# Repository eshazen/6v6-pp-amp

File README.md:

# 10 WPC 6V6 push-pull amp

This is a proposed build of an amp for TV sound.  I've been using a
6V6 single-ended amp, which is OK but perhaps a little wimpy for this
application.  The Dynaco A-410 EL84/6V6 schematic looks like a nice,
classic option.

As of 2026-04-02:

DigiKey parts are about $560 including iron.

Tubes:

    JJ 6SL7 2 @ $26.95  $45
    JJ 6V6  4 @ $23.95  $96
    JJ GZ34 1 @ $21.95  $22
                 Total $163

PCBs from JLC almost $200 with shipping.
<br>PCBGOGO $178 with shipping
				 
So around $950 total without chassis. Amps are now expensive!

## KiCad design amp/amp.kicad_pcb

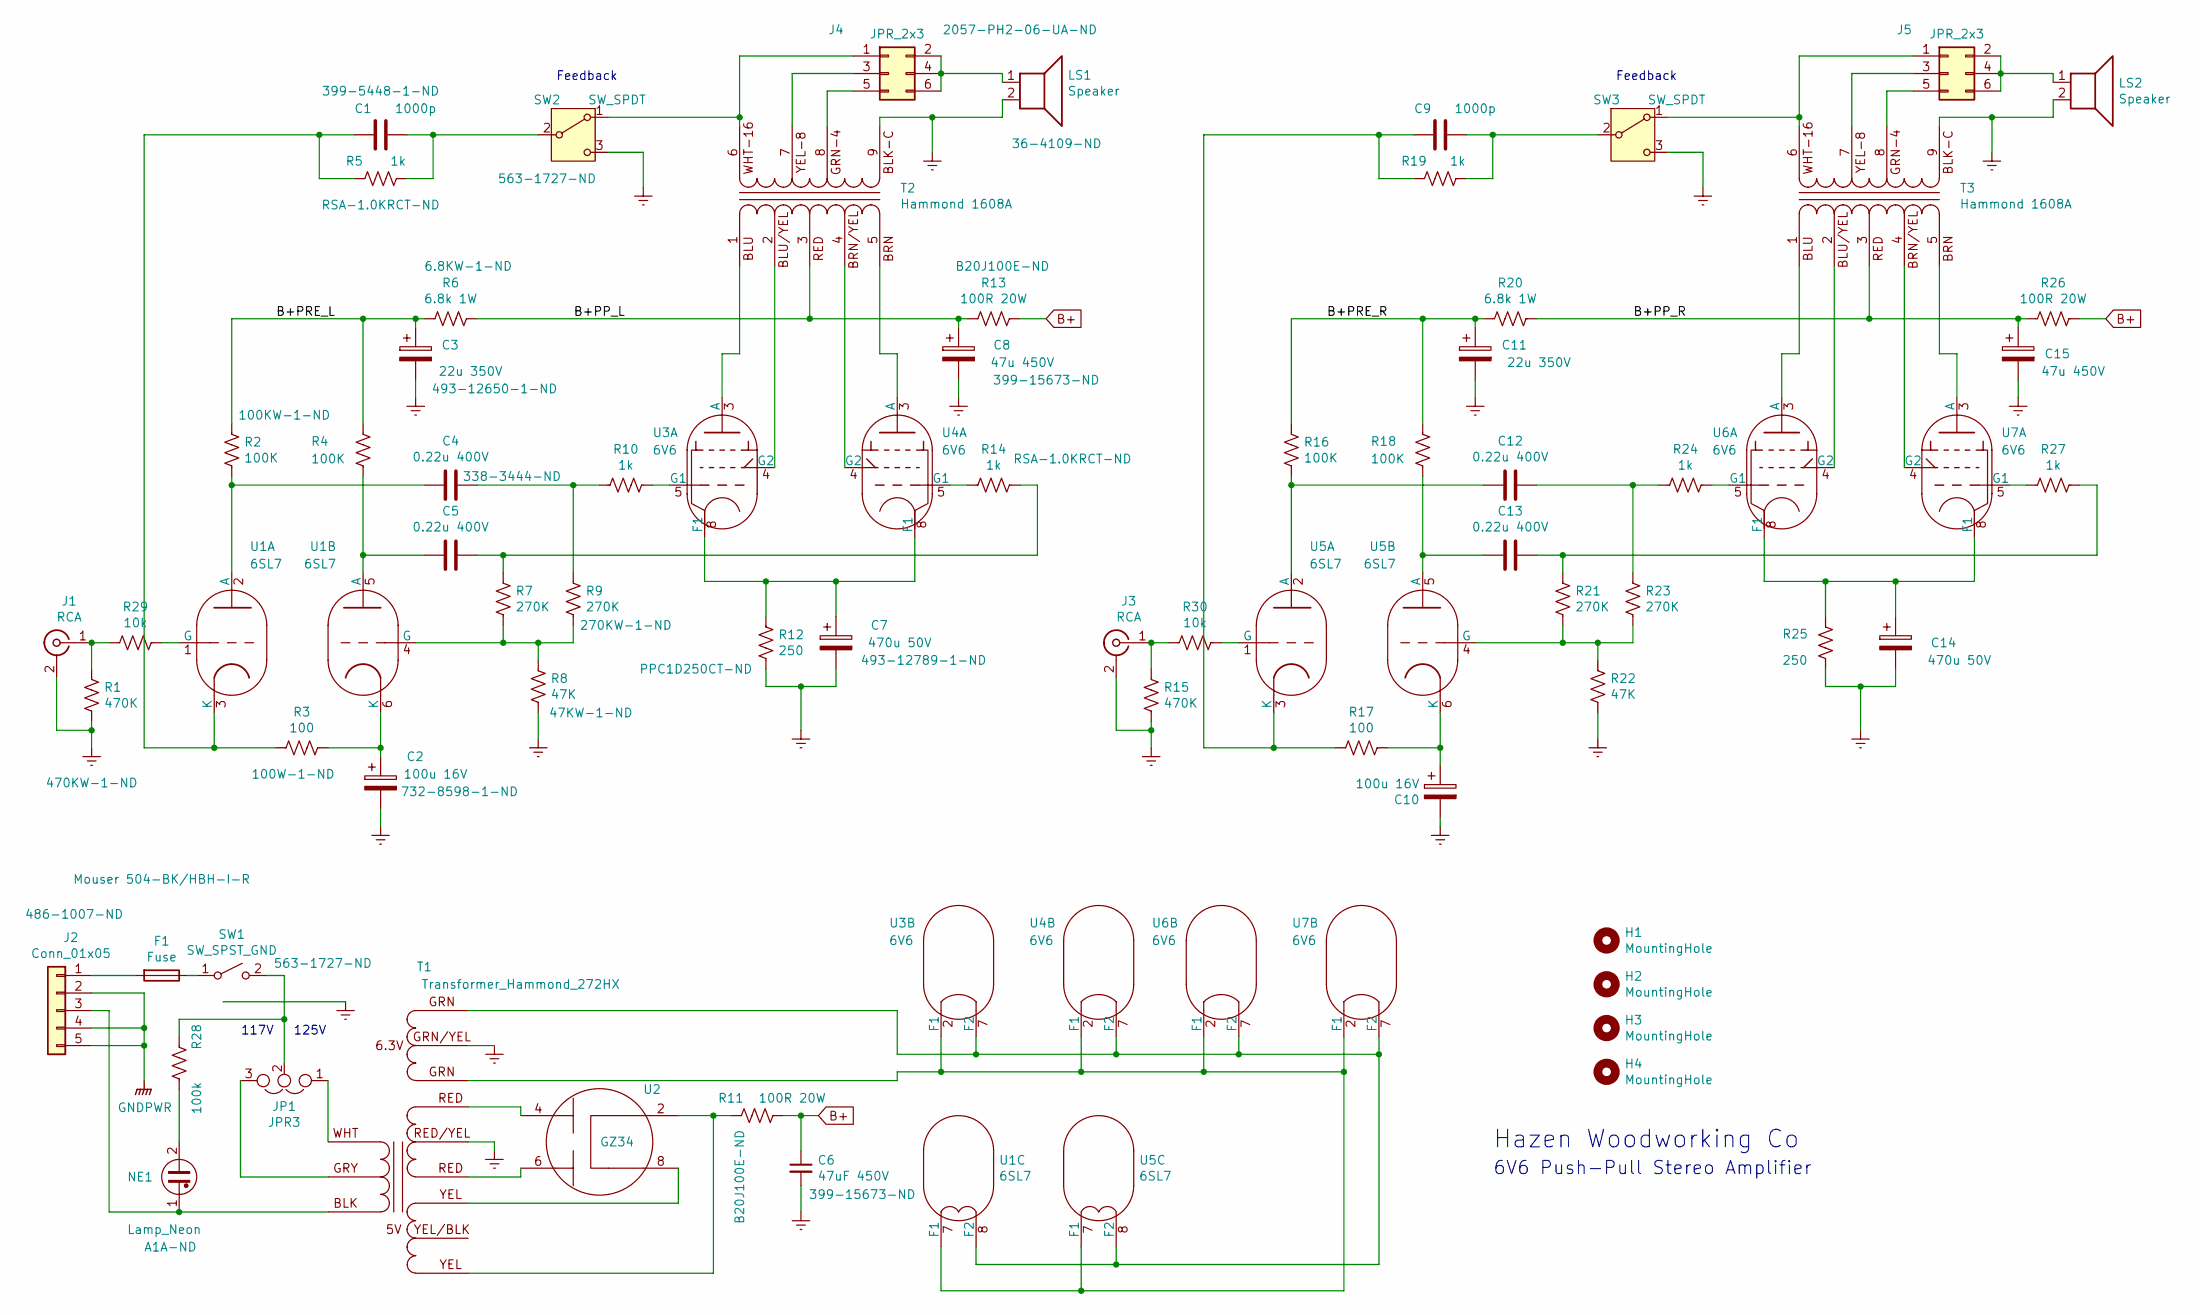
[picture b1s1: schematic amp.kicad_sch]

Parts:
C1, C9: 1000p; C_Rect_L7.2mm_W2.5mm_P5.00mm_FKS2_FKP2_MKS2_MKP2
C2, C10: 100u 16V; CP_Radial_D5.0mm_P2.00mm
C3, C11: 22u 350V; CP_Radial_D12.5mm_P5.00mm
C4, C5, C12, C13: 0.22u 400V; cap_rect_32x14_P18.3mm
C6: 47uF 450V; CP_Radial_D16.0mm_P7.50mm
C7, C14: 470u 50V; CP_Radial_D12.5mm_P5.00mm
C8, C15: 47u 450V; CP_Radial_D16.0mm_P7.50mm
F1: Fuse; HBH-I-R
H1, H2, H3, H4: MountingHole; Mtg6-32
J1, J3: RCA; PRJAN1X1
J2: Conn_01x05; GSP1.8101.1
J4, J5: JPR_2x3; PinHeader_2x03_P2.54mm_Vertical
JP1: JPR3; Molex_KK-396_A-41791-0003_1x03_P3.96mm_Vertical
LS1, LS2: Speaker; Keystone_4109
NE1: Lamp_Neon; A1A
R1, R15: 470K; R_Axial_DIN0411_L9.9mm_D3.6mm_P12.70mm_Horizontal
R2, R4, R16, R18: 100K; R_Axial_DIN0414_L11.9mm_D4.5mm_P15.24mm_Horizontal
R3, R17: 100; R_Axial_DIN0414_L11.9mm_D4.5mm_P15.24mm_Horizontal
R5, R10, R14, R19, R24, R27: 1k; R_Axial_DIN0411_L9.9mm_D3.6mm_P12.70mm_Horizontal
R6, R20: 6.8k 1W; R_Axial_DIN0414_L11.9mm_D4.5mm_P15.24mm_Horizontal
R7, R9, R21, R23: 270K; R_Axial_DIN0414_L11.9mm_D4.5mm_P15.24mm_Horizontal
R8, R22: 47K; R_Axial_DIN0411_L9.9mm_D3.6mm_P12.70mm_Horizontal
R11, R13, R26: 100R 20W; R_100R_20W_11x51mm
R12, R25: 250; R_Axial_DIN0414_L11.9mm_D4.5mm_P15.24mm_Horizontal
R28: 100k; R_Axial_DIN0414_L11.9mm_D4.5mm_P15.24mm_Horizontal
R29, R30: 10k; R_Axial_DIN0414_L11.9mm_D4.5mm_P15.24mm_Horizontal
SW1: SW_SPST_GND; 8GA1016-Z
SW2, SW3: SW_SPDT; 8GA1016-Z
T1: Transformer_Hammond_272HX; Hammond_272HX
T2, T3: Hammond 1608A; Hammond_1608A
U1, U5: 6SL7; Octal_Socket_P-ST8-193
U2: GZ34; Octal_Socket_P-ST8-193
U3, U4, U6, U7: 6V6; Octal_Socket_P-ST8-193

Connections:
/B+PP_L: C8.1, R6.1, R13.2, T2.3 (RED)
/B+PP_R: C15.1, R20.1, R26.2, T3.3 (RED)
/B+PRE_L: C3.1, R2.1, R4.1, R6.2
/B+PRE_R: C11.1, R16.1, R18.1, R20.2
B+: C6.1, R11.1, R13.1, R26.1
Earth: C2.2, C3.2, C6.2, C7.2, C8.2, C10.2, C11.2, C14.2, C15.2, J1.2 (Ext), J3.2 (Ext), LS1.2, LS2.2, R1.2, R8.2, R12.2, R15.2, R22.2, R25.2, SW1.4 (G1), SW2.3 (C), SW3.3 (C), T1.8 (SC), T1.11 (FC), T2.9 (BLK), T3.9 (BLK)
GNDPWR: J2.2, J2.4, J2.5
unnamed: C4.1, R9.1, R10.2
unnamed: C5.1, R7.1, R14.1
unnamed: C12.1, R23.1, R24.2
unnamed: C13.1, R21.1, R27.1
unnamed: J1.1 (In), R1.1, R29.2
unnamed: F1.2, J2.1
unnamed: J2.3, NE1.1, T1.3 (AB)
unnamed: J3.1 (In), R15.1, R30.2
unnamed: J4.1, SW2.1 (A), T2.6 (WHT)
unnamed: J4.2, J4.4, J4.6, LS1.1
unnamed: J4.3, T2.7 (YEL)
unnamed: J4.5, T2.8 (GRN)
unnamed: J5.1, SW3.1 (A), T3.6 (WHT)
unnamed: J5.2, J5.4, J5.6, LS2.1
unnamed: J5.3, T3.7 (YEL)
unnamed: J5.5, T3.8 (GRN)
unnamed: NE1.2, R28.1
unnamed: F1.1, SW1.1 (A)
unnamed: JP1.2, R28.2, SW1.2 (B)
unnamed: C1.1, R5.1, SW2.2 (B)
unnamed: C9.1, R19.1, SW3.2 (B)
unnamed: JP1.1, T1.1 (AA)
unnamed: JP1.3, T1.2 (AC)
unnamed: T1.10 (FA), U1.7 (F1), U3.2 (F1), U4.2 (F1), U5.7 (F1), U6.2 (F1), U7.2 (F1)
unnamed: T1.12 (FB), U1.8 (F2), U3.7 (F2), U4.7 (F2), U5.8 (F2), U6.7 (F2), U7.7 (F2)
unnamed: T2.1 (BLU), U3.3 (A)
unnamed: T2.2 (BLU/YEL), U3.4 (G2)
unnamed: T2.5 (BRN), U4.3 (A)
unnamed: T2.4 (BRN/YEL), U4.4 (G2)
unnamed: T3.1 (BLU), U6.3 (A)
unnamed: T3.2 (BLU/YEL), U6.4 (G2)
unnamed: T3.5 (BRN), U7.3 (A)
unnamed: T3.4 (BRN/YEL), U7.4 (G2)
unnamed: C4.2, R2.2, U1.2 (A)
unnamed: R29.1, U1.1 (G)
unnamed: C1.2, R3.2, R5.2, U1.3 (K)
unnamed: C5.2, R4.2, U1.5 (A)
unnamed: R7.2, R8.1, R9.2, U1.4 (G)
unnamed: C2.1, R3.1, U1.6 (K)
unnamed: T1.9 (SB), U2.4 (A1)
unnamed: T1.7 (SA), U2.6 (A2)
unnamed: T1.6 (SB), U2.8 (F2)
unnamed: R11.2, T1.4 (SA), U2.2 (K)
unnamed: C7.1, R12.1, U3.8 (F1), U4.8 (F1)
unnamed: R10.1, U3.5 (G1)
unnamed: R14.2, U4.5 (G1)
unnamed: C12.2, R16.2, U5.2 (A)
unnamed: R30.1, U5.1 (G)
unnamed: C9.2, R17.2, R19.2, U5.3 (K)
unnamed: C13.2, R18.2, U5.5 (A)
unnamed: R21.2, R22.1, R23.2, U5.4 (G)
unnamed: C10.1, R17.1, U5.6 (K)
unnamed: C14.1, R25.1, U6.8 (F1), U7.8 (F1)
unnamed: R24.1, U6.5 (G1)
unnamed: R27.2, U7.5 (G1)

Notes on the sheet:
117V
125V
Feedback
6V6 Push-Pull Stereo Amplifier
Hazen Woodworking Co

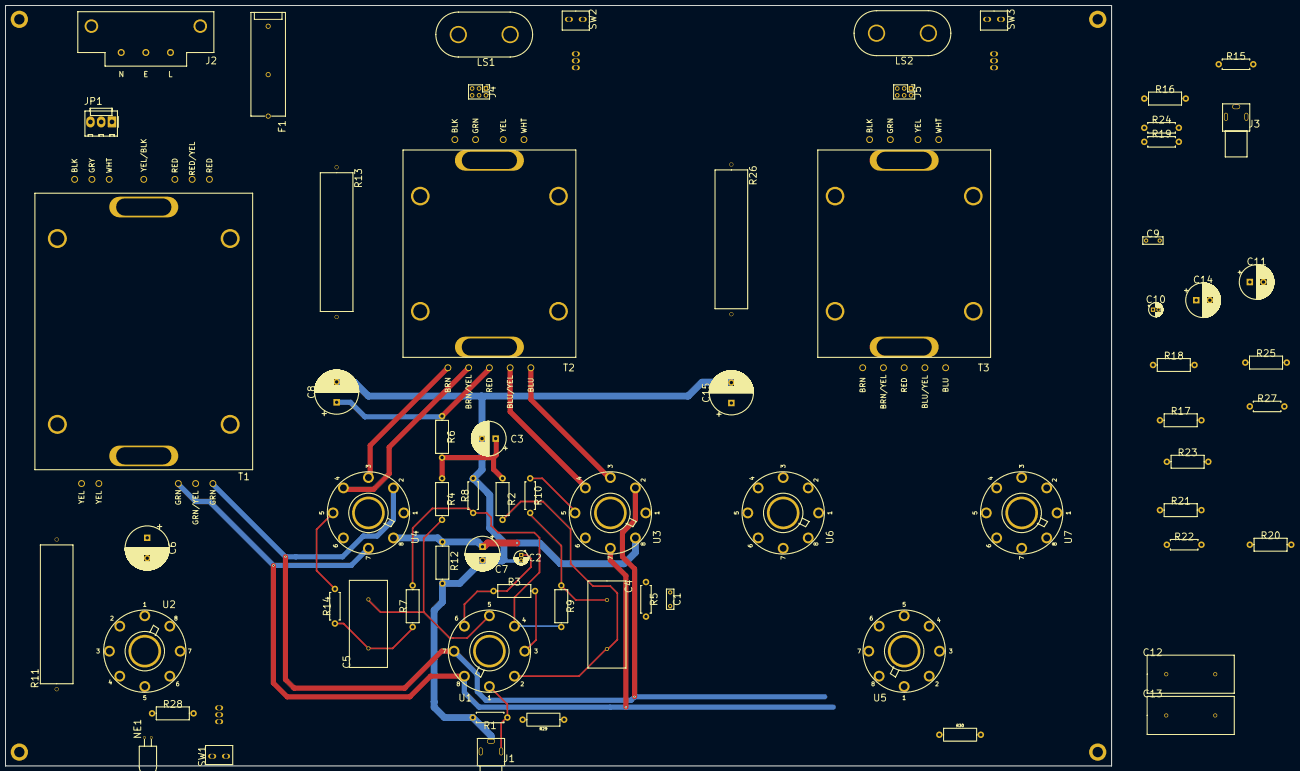
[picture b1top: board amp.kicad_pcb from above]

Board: 2 copper layers, 406.4 x 279.4 mm, 72 parts (0 on the bottom side), 62 nets.

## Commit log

2022-05-12 First draft amp schematic
2022-06-05 draft stereo schem complete
2022-06-06 starting footprints
2022-06-06 add library paths
2022-06-06 working on schem
2022-06-17 assigning part numbers
2022-06-17 All CatNo filled in
2022-07-18 all footprinted with a few issues
2022-07-18 placement
2022-07-19 starting 3D
2022-07-19 3D models
2022-07-19 3D work
2022-07-25 placement in progress
2022-08-18 tweaks
2022-08-18 draft routing one channel
2026-05-02 update notes and schematic
2026-05-02 notes and add grid stoppers to schem
2026-05-02 gitignore
